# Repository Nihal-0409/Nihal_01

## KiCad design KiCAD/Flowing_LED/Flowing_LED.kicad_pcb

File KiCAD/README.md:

# KiCAD
KiCAD Projects I have created

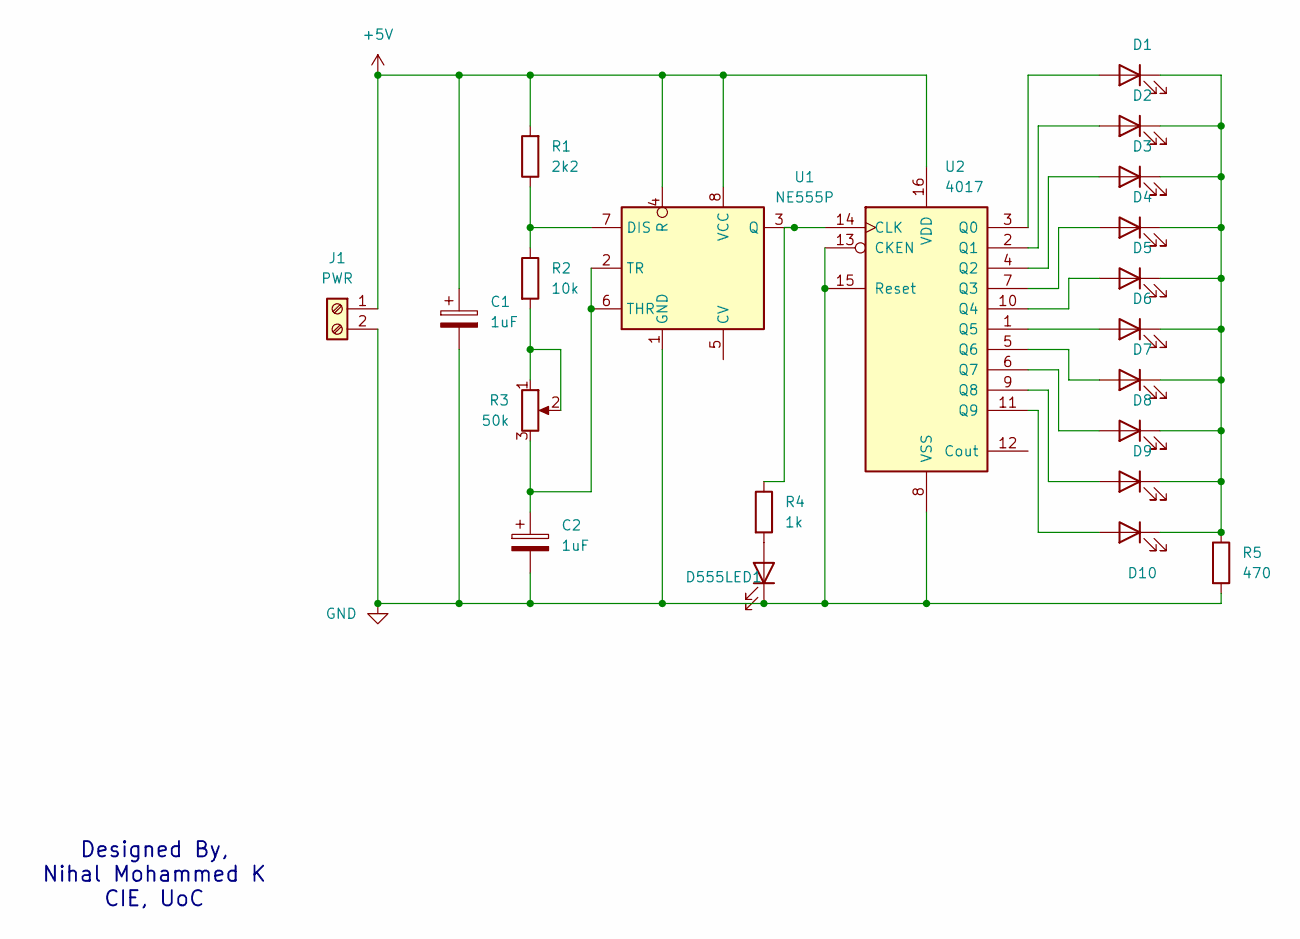
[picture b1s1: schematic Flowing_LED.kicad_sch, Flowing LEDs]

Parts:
C1, C2: 1uF; CP_Radial_D6.3mm_P2.50mm
D1, D2, D3, D4, D5, D6, D7, D8, D9, D10, D555LED1: LED; LED_D3.0mm
J1: PWR; TerminalBlock_Phoenix_MKDS-1,5-2-5.08_1x02_P5.08mm_Horizont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
R1: 2k2; R_Axial_DIN0207_L6.3mm_D2.5mm_P10.16mm_Horizontal
R2: 10k; R_Axial_DIN0207_L6.3mm_D2.5mm_P10.16mm_Horizontal
R3: 50k; Potentiometer_ACP_CA6-H2,5_Horizontal
R4: 1k; R_Axial_DIN0207_L6.3mm_D2.5mm_P10.16mm_Horizontal
R5: 470; R_Axial_DIN0207_L6.3mm_D2.5mm_P10.16mm_Horizontal
U1: NE555P; DIP-8_W7.62mm
U2: 4017; CERDIP-16_W7.62mm_SideBrazed_LongPads

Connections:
+5V: C1.1, J1.1, R1.2, U1.4 (R), U1.8 (VCC), U2.16 (VDD)
GND: C1.2, C2.2, D555LED1.1 (K), J1.2, R5.2, U1.1 (GND), U2.8 (VSS), U2.13 (CKEN), U2.15 (Reset)
unnamed: D1.2 (A), U2.3 (Q0)
unnamed: D1.1 (K), D2.1 (K), D3.1 (K), D4.1 (K), D5.1 (K), D6.1 (K), D7.1 (K), D8.1 (K), D9.1 (K), D10.1 (K), R5.1
unnamed: D2.2 (A), U2.2 (Q1)
unnamed: D3.2 (A), U2.4 (Q2)
unnamed: D4.2 (A), U2.7 (Q3)
unnamed: D5.2 (A), U2.10 (Q4)
unnamed: D6.2 (A), U2.1 (Q5)
unnamed: D7.2 (A), U2.5 (Q6)
unnamed: D8.2 (A), U2.6 (Q7)
unnamed: D9.2 (A), U2.9 (Q8)
unnamed: D10.2 (A), U2.11 (Q9)
unnamed: D555LED1.2 (A), R4.2
unnamed: R2.2, R3.1, R3.2
unnamed: R1.1, R2.1, U1.7 (DIS)
unnamed: R4.1, U1.3 (Q), U2.14 (CLK)
unnamed: C2.1, R3.3, U1.2 (TR), U1.6 (THR)

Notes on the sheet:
Designed By, Nihal Mohammed K CIE, UoC

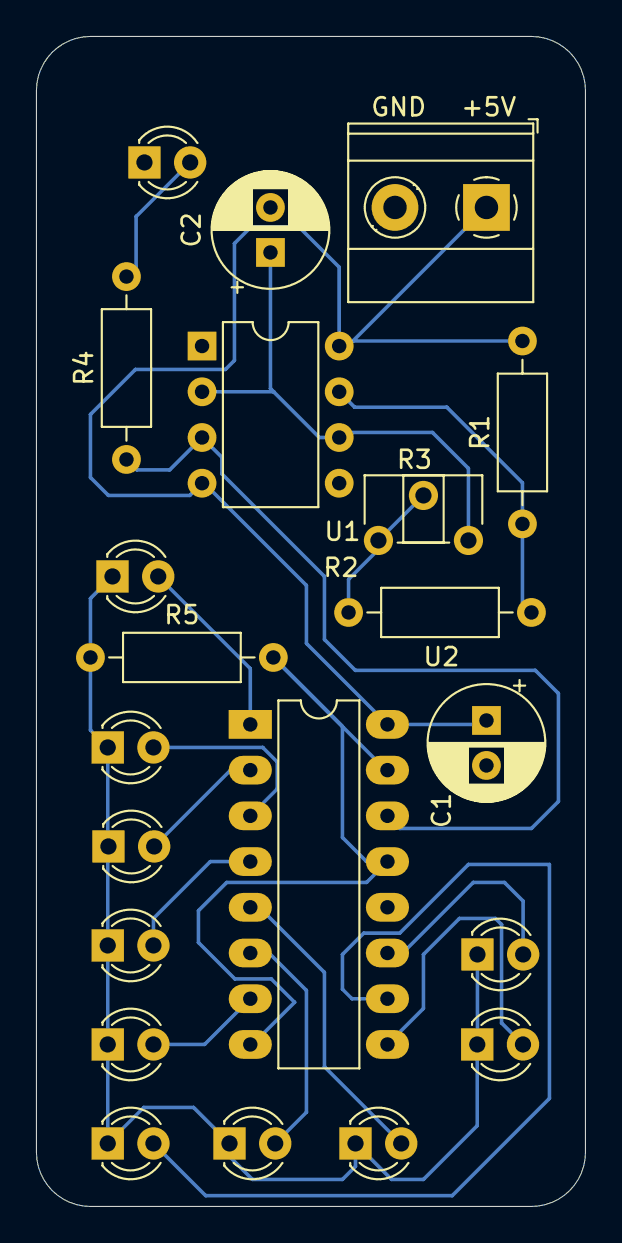
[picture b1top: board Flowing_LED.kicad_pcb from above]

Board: 2 copper layers, 30.5 x 65.0 mm, 21 parts (0 on the bottom side), 18 nets.

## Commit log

2025-02-28 Added some files & organized
2025-02-28 Created KiCAD File
